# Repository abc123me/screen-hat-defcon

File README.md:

# screen-hat-defcon

This is a collection of all the rpositories for the DEFCON screen hat

Name                                                                      | Description
--------------------------------------------------------------------------|------------------------------------------------
[screen-hat-rs](https://github.com/abc123me/screen-hat-rs)                | Userspace rust animation app
[fbgl-rs](https://github.com/abc123me/fbgl-rs)                            | Userspace rust graphics library
[ddmafb](https://github.com/abc123me/ddmafb)                              | Linux kernel direct DMA framebuffer driver
[Vivado project](https://github.com/abc123me/MicroPhaseZ7_Lite_ScreenHat) | Vivado project for the screen hat
[Vivado IP](https://github.com/abc123me/VivadoIP)                         | Vivado IP for the screen hat
[jlbsp](https://github.com/abc123me/jlbsp)                                | BSP for the screen-hat

## Hardware information

Wiring and other information is contained in the `ScreenHat.ods` spreadsheet. See the V2 page or picture below for complete information.

## GPIO expandsion PCB information

The 595pcb KiCAD project is the core GPIO expansion PCB used for backlight and reset 
control, gerber files for version 1 of the PCB are inside of `595pcb/grb_v1.zip` in this
repository, the BOM for the PCB is below:

Digikey part no                                                                                                 | Quantity | Description
----------------------------------------------------------------------------------------------------------------|----------|----------------------------------------------
[AP63203WU-7](https://www.digikey.com/en/products/detail/diodes-incorporated/AP63203WU-7/9858426)               | 1        | 3.3V 2A Buck converter
[74HC595DCT-ND](https://www.digikey.com/en/products/detail/toshiba-semiconductor-and-storage/74HC595D/5879984)  | 6        | 8-Bit Serial-In, Parallel-Out shift register
[T491S106K010AT](https://www.digikey.com/en/products/detail/toshiba-semiconductor-and-storage/74HC595D/5879984) | 4        | 10uF, 10V Tantalum capacitor
[478-KGM21NR71H104KTCT-ND](https://www.digikey.com/en/products/detail/kyocera-avx/KGM21NR71H104KT/563505)       | 10       | 100nF, 50V MLCC capacitor

## Displays used

 - The displays are 14x ILI9341 based 2.4" TFT LCDs, they're 240x320 and use a three-wire SPI interface. The SPI interface is unique as a word is 9-bits wide as opposed to the typical 8-bits.
 - The linux kernel driver always sends multiples of 9 bytes in order to meet this strange requirement of the SPI interface while using a typical 8-bit SPI driver.
 - The FPGA IP just does 9-bit SPI natively since it's an FPGA and I can make the hardware do whatever I want.

## Development board used

 - The MicroPhase Z7 lite is a cheap $100 chinese Zynq 7000 series development board, sometimes can be found for as cheap as $70
 - I am using the Zynq 7010 variant, the Zynq 7000 series has two 32-bit ARM V7 cores, this particular development board has 2Gib of RAM which.
 - This equates to 512MB of RAM in Linux (since 1B = 8b)
 - They don't provide a Vivado example for this board, I had to figure it all out myself, so videos on that below:
 - [Microphase Z7 lite DDR3 buildroot configuration](https://www.youtube.com/watch?v=MMN_5UOYHE4)
 - [Ethernet on MicroPhase Z7 lite](https://www.youtube.com/watch?v=It98w_9iQJE)
 - The DDR3 RAM on these chips is LPDDR3, I tried to get it to go as fast as I could but it is still pretty slow.
 - Never got USB to work, tried once, and gave up on it as I didn't have much interest in it since I never use USB anyways

### Potential improvements

The version 1 on the 595 expansion PCB worked almost perfectly however I suspect it could be improved.

 - Add a GPIO line to pin 6 of the AP632XX buck converter, so FPGA can contreol power for all screens, this would improve the initialization by making sure screens the screens are all turned on after the FPGA is fully loaded.
 - I2C ADC so voltages can be monitored
 - Global output enable controls for both shift register banks

# Building

## Dependencies

This is a buildroot project, meaning the entire linux kernel and all apps are built from source.

I use Arch btw, but last I checked Fedora is recommended for Linux kernel / Buildroot builds. Arch Linux typically has a GCC version that is too new, meaning you will be fighting GCC - so I wouldn't recommend it.

[Buildroot required dependencies](https://buildroot.org/downloads/manual/manual.html#requirement-mandatory)

My custom packages all use `git` so it is also a required package.

`fd-find` is required for my custom BSP repository and `bsp` script, if you have not used this unix `find` replacement, try it!

For any questions on how to modify packages, see [the buildroot manual](https://buildroot.org/downloads/manual/manual.html)

## Instructions

 1. Clone [jlbsp](https://github.com/abc123me/jlbsp)
 2. Enter the repository (`cd jlbsp`)
 3. Checkout the develop branch for latest (`git checkout develop`)
 4. Setup the screen hat BSP (`./bsp setup screen-hat`)
 5. Enter the screen hat BSP (`cd ../builds/screen-hat`)
 6. Turn off the `JL_SECRET_KEYS` repository via `make menuconfig`
 7. Build the BSP using `make all`
 8. Flash the SD card using `dd if=images/sdcard.img of=<my-sd-card> bs=4M oflag=sync status=progress`

## Troubleshooting

The `jlbsp` contains an upgrade script you can use to remotely upgrade the screen hat via `make deploy`.
The `bsps/screen-hat.bsp` file contains the IP address that would be used here. You'll also have to
setup SSH keys yourself by adding your SSH keys to the rootfs or enabling root login via SSH.

Serial via the USB UART may also be used, 115200 baud, the username is root, no password.

## Pictures

And yes, I know my camera is a potato, and no I will not be upgrading.

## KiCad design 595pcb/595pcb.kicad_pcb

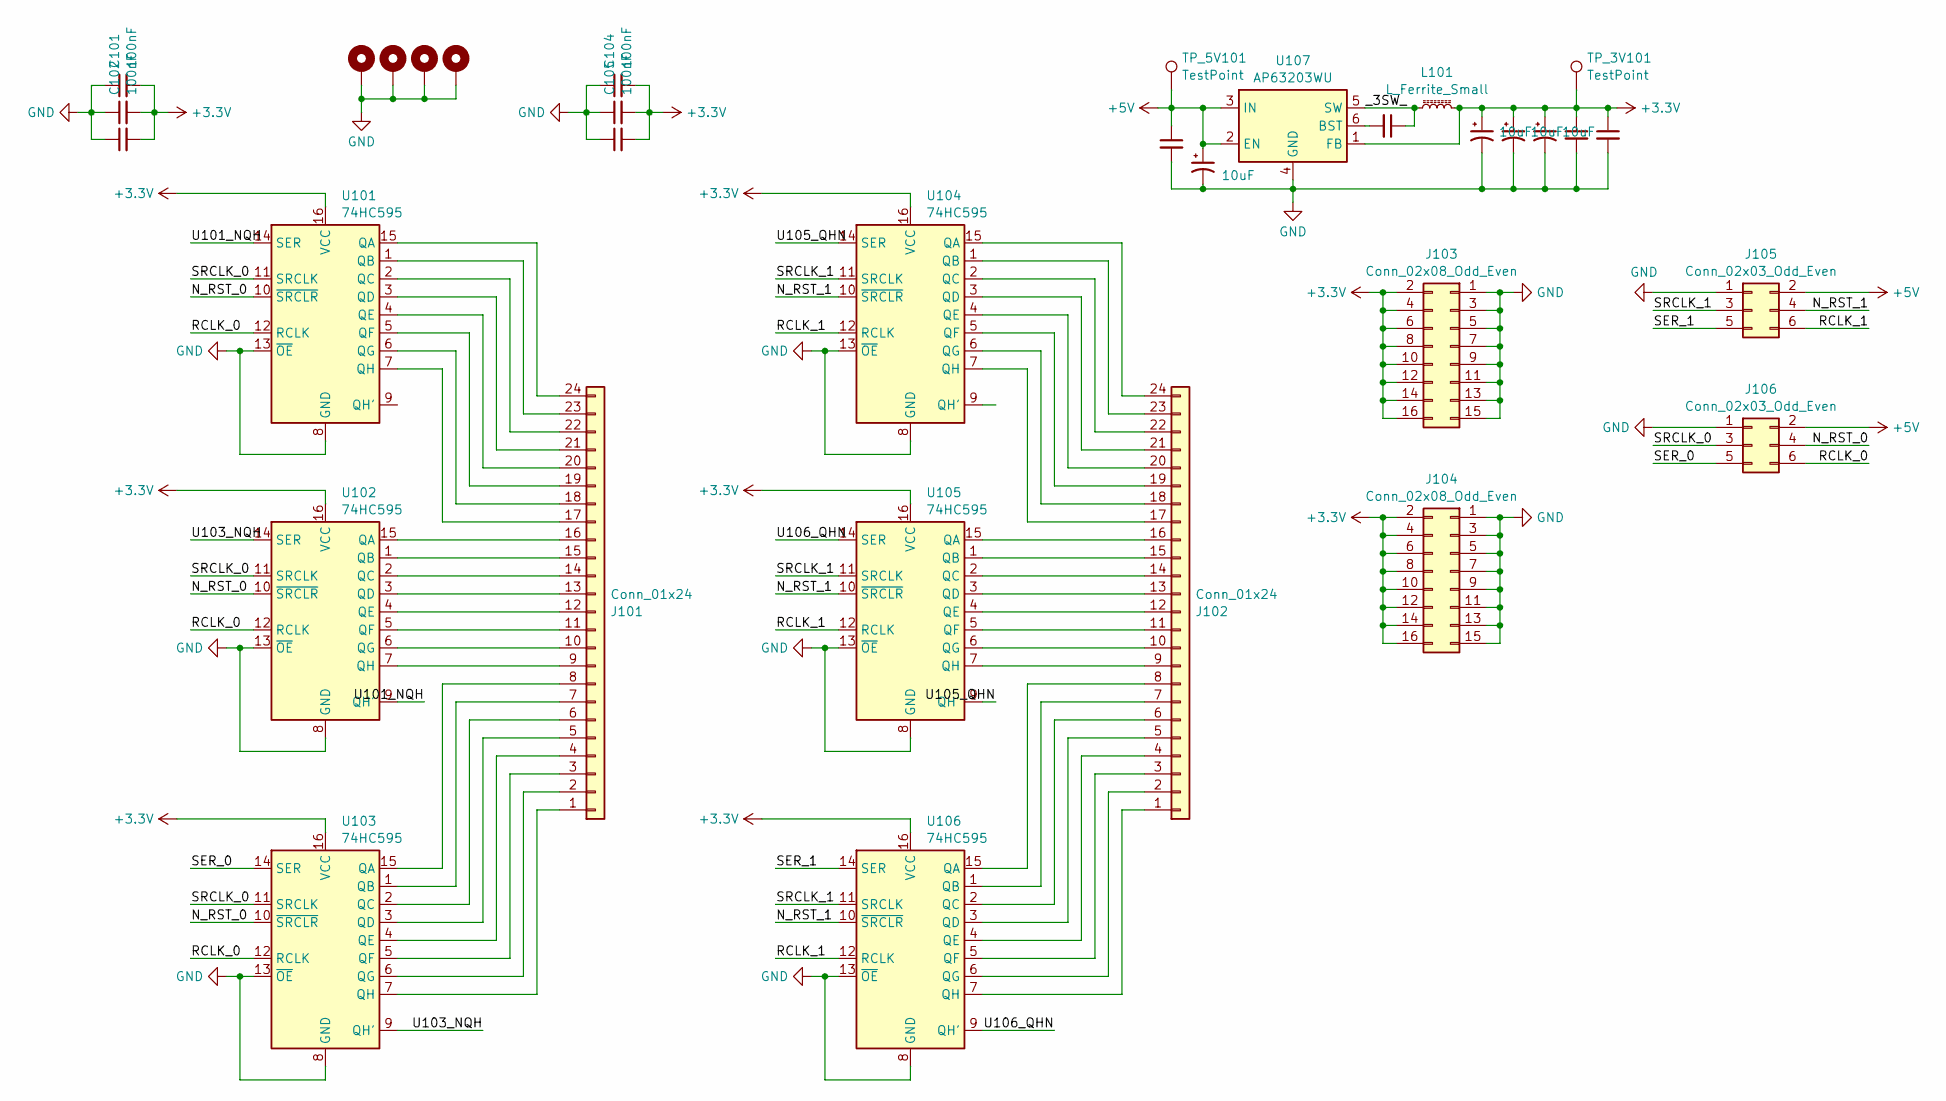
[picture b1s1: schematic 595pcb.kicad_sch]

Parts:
C101, C102, C103, C104, C105, C106, C107, C109, C113, C114: 100nF; C_0805_2012Metric
C108, C110, C111, C112: 10uF; CP_EIA-3216-12_Kemet-S
H101, H102, H103, H104: MountingHole_Pad; MountingHole_2.7mm_M2.5_Pad_Via
J101, J102: Conn_01x24; PinHeader_1x24_P2.54mm_Horizontal
J103, J104: Conn_02x08_Odd_Even; PinHeader_2x08_P2.54mm_Horizontal
J105, J106: Conn_02x03_Odd_Even; PinHeader_2x03_P2.54mm_Horizontal
L101: L_Ferrite_Small; L_Changjiang_FNR5045S
TP_3V101, TP_5V101: TestPoint; TestPoint_THTPad_1.0x1.0mm_Drill0.5mm
U101, U102, U103, U104, U105, U106: 74HC595; SOIC-16_3.9x9.9mm_P1.27mm
U107: AP63203WU; TSOT-23-6

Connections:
+3.3V: C101.2, C102.2, C103.2, C104.2, C105.2, C106.2, C110.1, C111.1, C112.1, C113.1, C114.1, J103.2, J103.4, J103.6, J103.8, J103.10, J103.12, J103.14, J103.16, J104.2, J104.4, J104.6, J104.8, J104.10, J104.12, J104.14, J104.16, L101.2, TP_3V101.1, U101.16 (VCC), U102.16 (VCC), U103.16 (VCC), U104.16 (VCC), U105.16 (VCC), U106.16 (VCC), U107.1 (FB)
+5V: C107.1, C108.1, J105.2, J106.2, TP_5V101.1, U107.2 (EN), U107.3 (IN)
/N_RST_0: J106.4, U101.10 (~SRCLR), U102.10 (~SRCLR), U103.10 (~SRCLR)
/N_RST_1: J105.4, U104.10 (~SRCLR), U105.10 (~SRCLR), U106.10 (~SRCLR)
/RCLK_0: J106.6, U101.12 (RCLK), U102.12 (RCLK), U103.12 (RCLK)
/RCLK_1: J105.6, U104.12 (RCLK), U105.12 (RCLK), U106.12 (RCLK)
/SER_0: J106.5, U103.14 (SER)
/SER_1: J105.5, U106.14 (SER)
/SRCLK_0: J106.3, U101.11 (SRCLK), U102.11 (SRCLK), U103.11 (SRCLK)
/SRCLK_1: J105.3, U104.11 (SRCLK), U105.11 (SRCLK), U106.11 (SRCLK)
/U101_NQH: U101.14 (SER), U102.9 (QH')
/U103_NQH: U102.14 (SER), U103.9 (QH')
/U105_QHN: U104.14 (SER), U105.9 (QH')
/U106_QHN: U105.14 (SER), U106.9 (QH')
/_3SW_: C109.1, L101.1, U107.5 (SW)
GND: C101.1, C102.1, C103.1, C104.1, C105.1, C106.1, C107.2, C108.2, C110.2, C111.2, C112.2, C113.2, C114.2, H101.1, H102.1, H103.1, H104.1, J103.1, J103.3, J103.5, J103.7, J103.9, J103.11, J103.13, J103.15, J104.1, J104.3, J104.5, J104.7, J104.9, J104.11, J104.13, J104.15, J105.1, J106.1, U101.8 (GND), U101.13 (~OE), U102.8 (GND), U102.13 (~OE), U103.8 (GND), U103.13 (~OE), U104.8 (GND), U104.13 (~OE), U105.8 (GND), U105.13 (~OE), U106.8 (GND), U106.13 (~OE), U107.4 (GND)
unnamed: J101.1, U103.7 (QH)
unnamed: J101.2, U103.6 (QG)
unnamed: J101.3, U103.5 (QF)
unnamed: J101.4, U103.4 (QE)
unnamed: J101.5, U103.3 (QD)
unnamed: J101.6, U103.2 (QC)
unnamed: J101.7, U103.1 (QB)
unnamed: J101.8, U103.15 (QA)
unnamed: J101.9, U102.7 (QH)
unnamed: J101.10, U102.6 (QG)
unnamed: J101.11, U102.5 (QF)
unnamed: J101.12, U102.4 (QE)
unnamed: J101.13, U102.3 (QD)
unnamed: J101.14, U102.2 (QC)
unnamed: J101.15, U102.1 (QB)
unnamed: J101.16, U102.15 (QA)
unnamed: J101.17, U101.7 (QH)
unnamed: J101.18, U101.6 (QG)
unnamed: J101.19, U101.5 (QF)
unnamed: J101.20, U101.4 (QE)
unnamed: J101.21, U101.3 (QD)
unnamed: J101.22, U101.2 (QC)
unnamed: J101.23, U101.1 (QB)
unnamed: J101.24, U101.15 (QA)
unnamed: J102.1, U106.7 (QH)
unnamed: J102.2, U106.6 (QG)
unnamed: J102.3, U106.5 (QF)
unnamed: J102.4, U106.4 (QE)
unnamed: J102.5, U106.3 (QD)
unnamed: J102.6, U106.2 (QC)
unnamed: J102.7, U106.1 (QB)
unnamed: J102.8, U106.15 (QA)
unnamed: J102.9, U105.7 (QH)
unnamed: J102.10, U105.6 (QG)
unnamed: J102.11, U105.5 (QF)
unnamed: J102.12, U105.4 (QE)
unnamed: J102.13, U105.3 (QD)
unnamed: J102.14, U105.2 (QC)
unnamed: J102.15, U105.1 (QB)
unnamed: J102.16, U105.15 (QA)
unnamed: J102.17, U104.7 (QH)
unnamed: J102.18, U104.6 (QG)
unnamed: J102.19, U104.5 (QF)
unnamed: J102.20, U104.4 (QE)
unnamed: J102.21, U104.3 (QD)
unnamed: J102.22, U104.2 (QC)
unnamed: J102.23, U104.1 (QB)
unnamed: J102.24, U104.15 (QA)
unnamed: C109.2, U107.6 (BST)

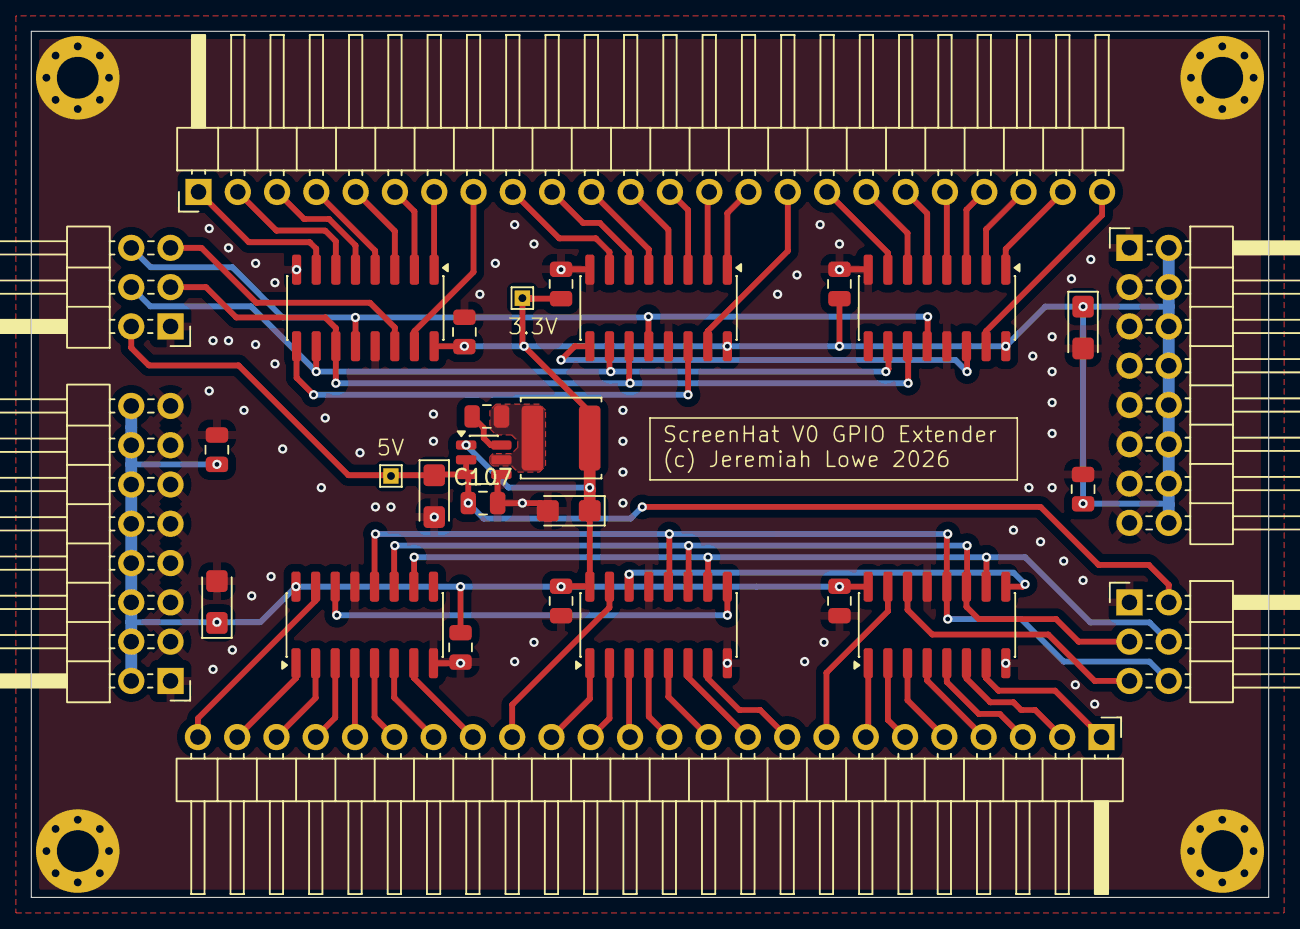
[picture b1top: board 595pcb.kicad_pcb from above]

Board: 2 copper layers, 80.0 x 56.0 mm, 34 parts (0 on the bottom side), 65 nets.
